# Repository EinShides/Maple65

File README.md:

A 65% standard single layout PCB that supports both cherry and alps switches. Uses USB mini with no ESD protection diode. PCB has been tested and is working.

Application: KiCad
Version: (5.1.5)-3, release build
Libraries:
    wxWidgets 3.0.4
    libcurl/7.66.0 OpenSSL/1.1.1d (Schannel) zlib/1.2.11 brotli/1.0.7 libidn2/2.2.0 libpsl/0.21.0 (+libidn2/2.1.1) nghttp2/1.39.2
Platform: Windows 8 (build 9200), 64-bit edition, 64 bit, Little endian, wxMSW
Build Info:
    wxWidgets: 3.0.4 (wchar_t,wx containers,compatible with 2.8)
    Boost: 1.71.0
    OpenCASCADE Community Edition: 6.9.1
    Curl: 7.66.0
    Compiler: GCC 9.2.0 with C++ ABI 1013

Build settings:
    USE_WX_GRAPHICS_CONTEXT=OFF
    USE_WX_OVERLAY=OFF
    KICAD_SCRIPTING=ON
    KICAD_SCRIPTING_MODULES=ON
    KICAD_SCRIPTING_PYTHON3=OFF
    KICAD_SCRIPTING_WXPYTHON=ON
    KICAD_SCRIPTING_WXPYTHON_PHOENIX=OFF
    KICAD_SCRIPTING_ACTION_MENU=ON
    BUILD_GITHUB_PLUGIN=ON
    KICAD_USE_OCE=ON
    KICAD_USE_OCC=OFF
    KICAD_SPICE=ON

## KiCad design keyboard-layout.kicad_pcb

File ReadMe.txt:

The Maple65 Keyboard is a 65% keyboard (303x94mm) that is based off of the Tada68 (same mounting holes and default layout)

IMPORTANT: Make sure to check and meet the design rules of the chosen pcb manufacturer before ordering or else errors may occur.
		e.g. OSH Park requires a Pad Mask Clearance of 0.0508mm

This CAD file was created in Kicad version (5.1.5)-3, release build.

Application: KiCad
Version: (5.1.5)-3, release build
Libraries:
    wxWidgets 3.0.4
    libcurl/7.66.0 OpenSSL/1.1.1d (Schannel) zlib/1.2.11 brotli/1.0.7 libidn2/2.2.0 libpsl/0.21.0 (+libidn2/2.1.1) nghttp2/1.39.2
Platform: Windows 8 (build 9200), 64-bit edition, 64 bit, Little endian, wxMSW
Build Info:
    wxWidgets: 3.0.4 (wchar_t,wx containers,compatible with 2.8)
    Boost: 1.71.0
    OpenCASCADE Community Edition: 6.9.1
    Curl: 7.66.0
    Compiler: GCC 9.2.0 with C++ ABI 1013

Build settings:
    USE_WX_GRAPHICS_CONTEXT=OFF
    USE_WX_OVERLAY=OFF
    KICAD_SCRIPTING=ON
    KICAD_SCRIPTING_MODULES=ON
    KICAD_SCRIPTING_PYTHON3=OFF
    KICAD_SCRIPTING_WXPYTHON=ON
    KICAD_SCRIPTING_WXPYTHON_PHOENIX=OFF
    KICAD_SCRIPTING_ACTION_MENU=ON
    BUILD_GITHUB_PLUGIN=ON
    KICAD_USE_OCE=ON
    KICAD_USE_OCC=OFF
    KICAD_SPICE=ON

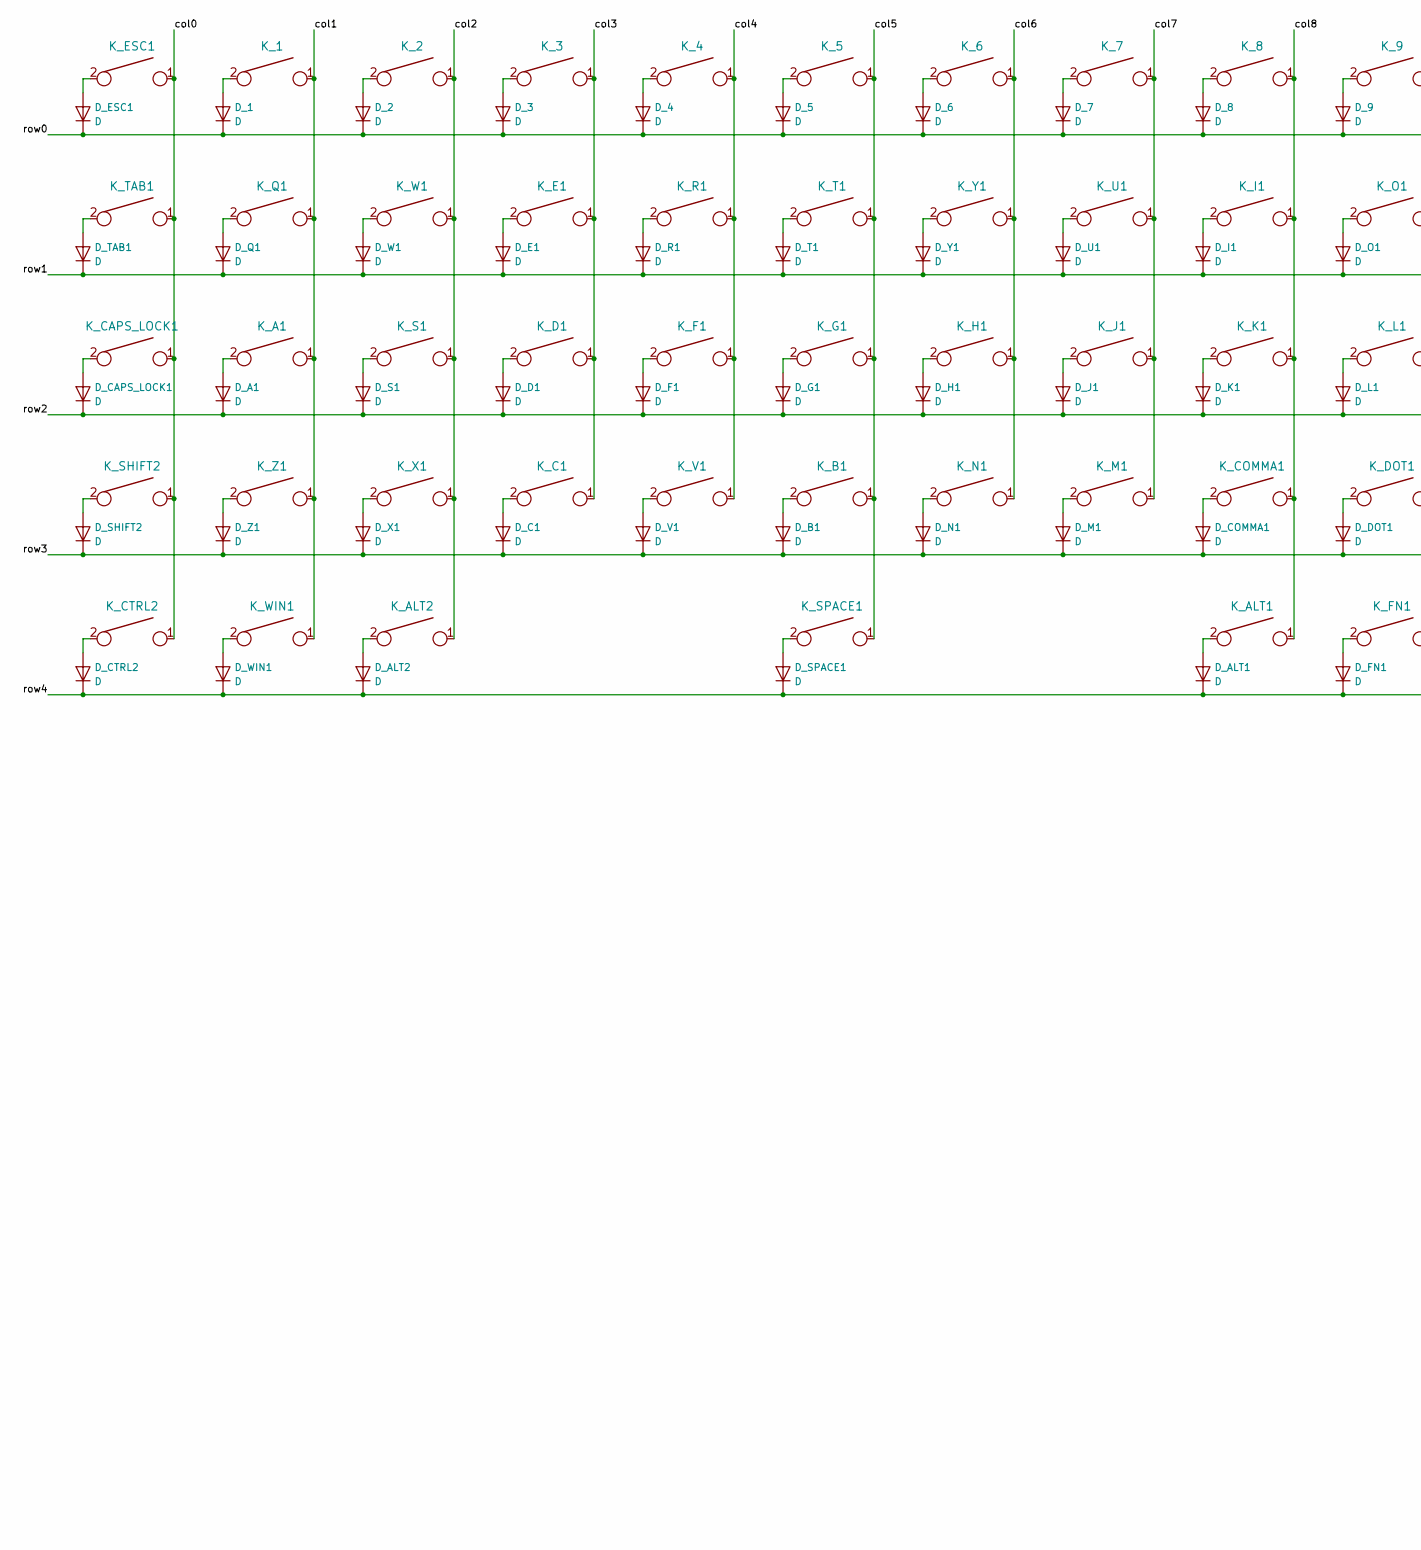
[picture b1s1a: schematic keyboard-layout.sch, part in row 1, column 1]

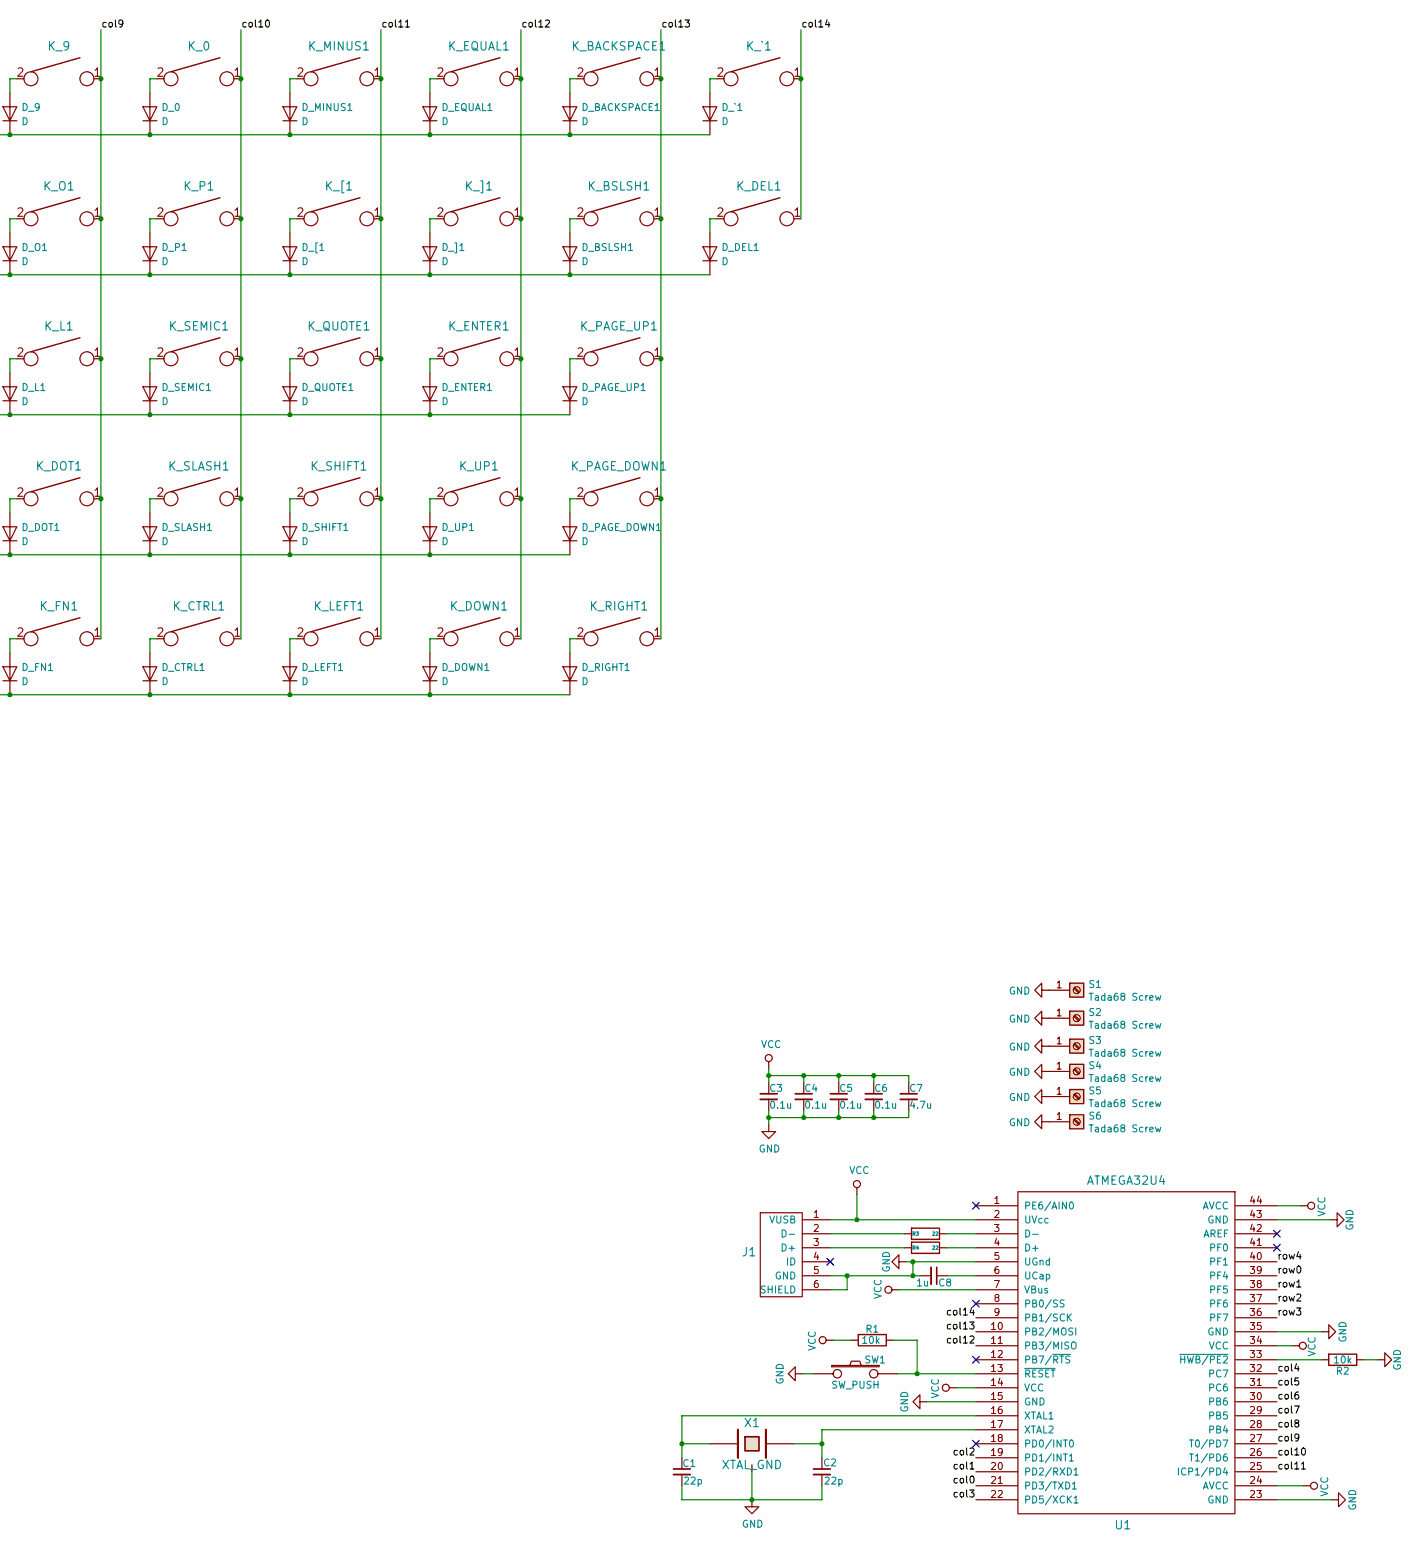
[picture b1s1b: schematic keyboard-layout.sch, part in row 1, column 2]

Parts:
C1, C2: 22p; C_0805_2012Metric_Pad1.15x1.40mm_HandSolder
C3, C4, C5, C6: 0.1u; C_0805_2012Metric_Pad1.15x1.40mm_HandSolder
C7: 4.7u; C_0805_2012Metric_Pad1.15x1.40mm_HandSolder
C8: 1u; C_0805_2012Metric_Pad1.15x1.40mm_HandSolder
D_0, D_1, D_2, D_3, D_4, D_5, D_6, D_7, D_8, D_9: D; D_SOD123_axial
D_A1: D; D_SOD123_axial
D_ALT1, D_ALT2: D; D_SOD123_axial
D_B1: D; D_SOD123_axial
D_BACKSPACE1: D; D_SOD123_axial
D_BSLSH1: D; D_SOD123_axial
D_C1: D; D_SOD123_axial
D_CAPS_LOCK1: D; D_SOD123_axial
D_COMMA1: D; D_SOD123_axial
D_CTRL1, D_CTRL2: D; D_SOD123_axial
D_D1: D; D_SOD123_axial
D_DEL1: D; D_SOD123_axial
D_DOT1: D; D_SOD123_axial
D_DOWN1: D; D_SOD123_axial
D_E1: D; D_SOD123_axial
D_ENTER1: D; D_SOD123_axial
D_EQUAL1: D; D_SOD123_axial
D_ESC1: D; D_SOD123_axial
D_F1: D; D_SOD123_axial
D_FN1: D; D_SOD123_axial
D_G1: D; D_SOD123_axial
D_H1: D; D_SOD123_axial
D_I1: D; D_SOD123_axial
D_J1: D; D_SOD123_axial
D_K1: D; D_SOD123_axial
D_L1: D; D_SOD123_axial
D_LEFT1: D; D_SOD123_axial
D_M1: D; D_SOD123_axial
D_MINUS1: D; D_SOD123_axial
D_N1: D; D_SOD123_axial
D_O1: D; D_SOD123_axial
D_P1: D; D_SOD123_axial
D_PAGE_DOWN1: D; D_SOD123_axial
D_PAGE_UP1: D; D_SOD123_axial
D_Q1: D; D_SOD123_axial
D_QUOTE1: D; D_SOD123_axial
D_R1: D; D_SOD123_axial
D_RIGHT1: D; D_SOD123_axial
D_S1: D; D_SOD123_axial
D_SEMIC1: D; D_SOD123_axial
D_SHIFT1, D_SHIFT2: D; D_SOD123_axial
D_SLASH1: D; D_SOD123_axial
D_SPACE1: D; D_SOD123_axial
D_T1: D; D_SOD123_axial
D_TAB1: D; D_SOD123_axial
D_U1: D; D_SOD123_axial
D_UP1: D; D_SOD123_axial
D_V1: D; D_SOD123_axial
D_W1: D; D_SOD123_axial
D_WIN1: D; D_SOD123_axial
D_X1: D; D_SOD123_axial
D_Y1: D; D_SOD123_axial
D_Z1: D; D_SOD123_axial
D_[1: D; D_SOD123_axial
D_]1: D; D_SOD123_axial
D_`1: D; D_SOD123_axial
J1: USB_mini_micro_B; USB_miniB_hirose_5S8
K_0, K_1, K_2, K_3, K_4, K_5, K_6, K_7, K_8, K_9: KEYSW; MX-1U-NoLED
K_A1: KEYSW; MX-1U-NoLED
K_ALT1: KEYSW; MX-1U-NoLED
K_ALT2: KEYSW; MX-1.25U-NoLED
K_B1: KEYSW; MX-1U-NoLED
K_BACKSPACE1: KEYSW; MX-2U-NoLED
K_BSLSH1: KEYSW; MX-1.5U-NoLED
K_C1: KEYSW; MX-1U-NoLED
K_CAPS_LOCK1: KEYSW; MX-1.75U-NoLED
K_COMMA1: KEYSW; MX-1U-NoLED
K_CTRL1: KEYSW; MX-1U-NoLED
K_CTRL2: KEYSW; MX-1.25U-NoLED
K_D1: KEYSW; MX-1U-NoLED
K_DEL1: KEYSW; MX-1U-NoLED
K_DOT1: KEYSW; MX-1U-NoLED
K_DOWN1: KEYSW; MX-1U-NoLED
K_E1: KEYSW; MX-1U-NoLED
K_ENTER1: KEYSW; MX-2.25U-NoLED
K_EQUAL1: KEYSW; MX-1U-NoLED
K_ESC1: KEYSW; MX-1U-NoLED
K_F1: KEYSW; MX-1U-NoLED
K_FN1: KEYSW; MX-1U-NoLED
K_G1: KEYSW; MX-1U-NoLED
K_H1: KEYSW; MX-1U-NoLED
K_I1: KEYSW; MX-1U-NoLED
K_J1: KEYSW; MX-1U-NoLED
K_K1: KEYSW; MX-1U-NoLED
K_L1: KEYSW; MX-1U-NoLED
K_LEFT1: KEYSW; MX-1U-NoLED
K_M1: KEYSW; MX-1U-NoLED
K_MINUS1: KEYSW; MX-1U-NoLED
K_N1: KEYSW; MX-1U-NoLED
K_O1: KEYSW; MX-1U-NoLED
K_P1: KEYSW; MX-1U-NoLED
K_PAGE_DOWN1: KEYSW; MX-1U-NoLED
K_PAGE_UP1: KEYSW; MX-1U-NoLED
K_Q1: KEYSW; MX-1U-NoLED
K_QUOTE1: KEYSW; MX-1U-NoLED
K_R1: KEYSW; MX-1U-NoLED
K_RIGHT1: KEYSW; MX-1U-NoLED
K_S1: KEYSW; MX-1U-NoLED
K_SEMIC1: KEYSW; MX-1U-NoLED
K_SHIFT1: KEYSW; MX-1.75U-NoLED
K_SHIFT2: KEYSW; MX-2.25U-NoLED
K_SLASH1: KEYSW; MX-1U-NoLED
K_SPACE1: KEYSW; MX-6.25U-ReversedStabilizers-NoLED
K_T1: KEYSW; MX-1U-NoLED
K_TAB1: KEYSW; MX-1.5U-NoLED
K_U1: KEYSW; MX-1U-NoLED
K_UP1: KEYSW; MX-1U-NoLED
K_V1: KEYSW; MX-1U-NoLED
K_W1: KEYSW; MX-1U-NoLED
K_WIN1: KEYSW; MX-1.25U-NoLED
K_X1: KEYSW; MX-1U-NoLED
K_Y1: KEYSW; MX-1U-NoLED
K_Z1: KEYSW; MX-1U-NoLED
K_[1: KEYSW; MX-1U-NoLED
K_]1: KEYSW; MX-1U-NoLED
K_`1: KEYSW; MX-1U-NoLED
R1, R2: 10k; R_0805_2012Metric_Pad1.15x1.40mm_HandSolder
R3, R4: 22; R_0805_2012Metric_Pad1.15x1.40mm_HandSolder
S1, S2, S3, S4, S5, S6: Tada68 Screw; 5.5_5x2.5mm
SW1: SW_PUSH; SW_SPST_TL3342
U1: ATMEGA32U4; TQFP-44_10x10mm_Pitch0.8mm
X1: XTAL_GND; crystal_FA238-TSX3225

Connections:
/col0: K_CAPS_LOCK1.1, K_CTRL2.1, K_ESC1.1, K_SHIFT2.1, K_TAB1.1, U1.21 (PD3/TXD1)
/col1: K_1.1, K_A1.1, K_Q1.1, K_WIN1.1, K_Z1.1, U1.20 (PD2/RXD1)
/col2: K_2.1, K_ALT2.1, K_S1.1, K_W1.1, K_X1.1, U1.19 (PD1/INT1)
/col3: K_3.1, K_C1.1, K_D1.1, K_E1.1, U1.22 (PD5/XCK1)
/col4: K_4.1, K_F1.1, K_R1.1, K_V1.1, U1.32 (PC7)
/col5: K_5.1, K_B1.1, K_G1.1, K_SPACE1.1, K_T1.1, U1.31 (PC6)
/col6: K_6.1, K_H1.1, K_N1.1, K_Y1.1, U1.30 (PB6)
/col7: K_7.1, K_J1.1, K_M1.1, K_U1.1, U1.29 (PB5)
/col8: K_8.1, K_ALT1.1, K_COMMA1.1, K_I1.1, K_K1.1, U1.28 (PB4)
/col9: K_9.1, K_DOT1.1, K_FN1.1, K_L1.1, K_O1.1, U1.27 (T0/PD7)
/col10: K_0.1, K_CTRL1.1, K_P1.1, K_SEMIC1.1, K_SLASH1.1, U1.26 (T1/PD6)
/col11: K_LEFT1.1, K_MINUS1.1, K_QUOTE1.1, K_SHIFT1.1, K_[1.1, U1.25 (ICP1/PD4)
/col12: K_DOWN1.1, K_ENTER1.1, K_EQUAL1.1, K_UP1.1, K_]1.1, U1.11 (PB3/MISO)
/col13: K_BACKSPACE1.1, K_BSLSH1.1, K_PAGE_DOWN1.1, K_PAGE_UP1.1, K_RIGHT1.1, U1.10 (PB2/MOSI)
/col14: K_DEL1.1, K_`1.1, U1.9 (PB1/SCK)
/row0: D_0.1 (K), D_1.1 (K), D_2.1 (K), D_3.1 (K), D_4.1 (K), D_5.1 (K), D_6.1 (K), D_7.1 (K), D_8.1 (K), D_9.1 (K), D_BACKSPACE1.1 (K), D_EQUAL1.1 (K), D_ESC1.1 (K), D_MINUS1.1 (K), D_`1.1 (K), U1.39 (PF4)
/row1: D_BSLSH1.1 (K), D_DEL1.1 (K), D_E1.1 (K), D_I1.1 (K), D_O1.1 (K), D_P1.1 (K), D_Q1.1 (K), D_R1.1 (K), D_T1.1 (K), D_TAB1.1 (K), D_U1.1 (K), D_W1.1 (K), D_Y1.1 (K), D_[1.1 (K), D_]1.1 (K), U1.38 (PF5)
/row2: D_A1.1 (K), D_CAPS_LOCK1.1 (K), D_D1.1 (K), D_ENTER1.1 (K), D_F1.1 (K), D_G1.1 (K), D_H1.1 (K), D_J1.1 (K), D_K1.1 (K), D_L1.1 (K), D_PAGE_UP1.1 (K), D_QUOTE1.1 (K), D_S1.1 (K), D_SEMIC1.1 (K), U1.37 (PF6)
/row3: D_B1.1 (K), D_C1.1 (K), D_COMMA1.1 (K), D_DOT1.1 (K), D_M1.1 (K), D_N1.1 (K), D_PAGE_DOWN1.1 (K), D_SHIFT1.1 (K), D_SHIFT2.1 (K), D_SLASH1.1 (K), D_UP1.1 (K), D_V1.1 (K), D_X1.1 (K), D_Z1.1 (K), U1.36 (PF7)
/row4: D_ALT1.1 (K), D_ALT2.1 (K), D_CTRL1.1 (K), D_CTRL2.1 (K), D_DOWN1.1 (K), D_FN1.1 (K), D_LEFT1.1 (K), D_RIGHT1.1 (K), D_SPACE1.1 (K), D_WIN1.1 (K), U1.40 (PF1)
GND: C1.2, C2.2, C3.2, C4.2, C5.2, C6.2, C7.2, C8.2, J1.5 (GND), J1.6 (SHIELD), R2.1, S1.1, S2.1, S3.1, S4.1, S5.1, S6.1, SW1.1, U1.5 (UGnd), U1.15 (GND), U1.23 (GND), U1.35 (GND), U1.43 (GND), X1.3
unnamed: C1.1, U1.16 (XTAL1), X1.1
unnamed: C2.1, U1.17 (XTAL2), X1.2
unnamed: C8.1, U1.6 (UCap)
unnamed: D_0.2 (A), K_0.2
unnamed: D_1.2 (A), K_1.2
unnamed: D_2.2 (A), K_2.2
unnamed: D_3.2 (A), K_3.2
unnamed: D_4.2 (A), K_4.2
unnamed: D_5.2 (A), K_5.2
unnamed: D_6.2 (A), K_6.2
unnamed: D_7.2 (A), K_7.2
unnamed: D_8.2 (A), K_8.2
unnamed: D_9.2 (A), K_9.2
unnamed: D_A1.2 (A), K_A1.2
unnamed: D_ALT1.2 (A), K_ALT1.2
unnamed: D_ALT2.2 (A), K_ALT2.2
unnamed: D_B1.2 (A), K_B1.2
unnamed: D_BACKSPACE1.2 (A), K_BACKSPACE1.2
unnamed: D_BSLSH1.2 (A), K_BSLSH1.2
unnamed: D_C1.2 (A), K_C1.2
unnamed: D_CAPS_LOCK1.2 (A), K_CAPS_LOCK1.2
unnamed: D_COMMA1.2 (A), K_COMMA1.2
unnamed: D_CTRL1.2 (A), K_CTRL1.2
unnamed: D_CTRL2.2 (A), K_CTRL2.2
unnamed: D_D1.2 (A), K_D1.2
unnamed: D_DEL1.2 (A), K_DEL1.2
unnamed: D_DOT1.2 (A), K_DOT1.2
unnamed: D_DOWN1.2 (A), K_DOWN1.2
unnamed: D_E1.2 (A), K_E1.2
unnamed: D_ENTER1.2 (A), K_ENTER1.2
unnamed: D_EQUAL1.2 (A), K_EQUAL1.2
unnamed: D_ESC1.2 (A), K_ESC1.2
unnamed: D_F1.2 (A), K_F1.2
unnamed: D_FN1.2 (A), K_FN1.2
unnamed: D_G1.2 (A), K_G1.2
unnamed: D_H1.2 (A), K_H1.2
unnamed: D_I1.2 (A), K_I1.2
unnamed: D_J1.2 (A), K_J1.2
unnamed: D_K1.2 (A), K_K1.2
unnamed: D_L1.2 (A), K_L1.2
unnamed: D_LEFT1.2 (A), K_LEFT1.2
unnamed: D_M1.2 (A), K_M1.2
unnamed: D_MINUS1.2 (A), K_MINUS1.2
unnamed: D_N1.2 (A), K_N1.2
unnamed: D_O1.2 (A), K_O1.2
unnamed: D_P1.2 (A), K_P1.2
unnamed: D_PAGE_DOWN1.2 (A), K_PAGE_DOWN1.2
unnamed: D_PAGE_UP1.2 (A), K_PAGE_UP1.2
unnamed: D_Q1.2 (A), K_Q1.2
unnamed: D_QUOTE1.2 (A), K_QUOTE1.2
unnamed: D_R1.2 (A), K_R1.2
unnamed: D_RIGHT1.2 (A), K_RIGHT1.2
unnamed: D_S1.2 (A), K_S1.2
unnamed: D_SEMIC1.2 (A), K_SEMIC1.2
unnamed: D_SHIFT1.2 (A), K_SHIFT1.2
unnamed: D_SHIFT2.2 (A), K_SHIFT2.2
unnamed: D_SLASH1.2 (A), K_SLASH1.2
unnamed: D_SPACE1.2 (A), K_SPACE1.2
unnamed: D_T1.2 (A), K_T1.2
unnamed: D_TAB1.2 (A), K_TAB1.2
unnamed: D_U1.2 (A), K_U1.2
unnamed: D_UP1.2 (A), K_UP1.2
unnamed: D_V1.2 (A), K_V1.2
unnamed: D_W1.2 (A), K_W1.2
unnamed: D_WIN1.2 (A), K_WIN1.2
unnamed: D_X1.2 (A), K_X1.2
unnamed: D_Y1.2 (A), K_Y1.2
unnamed: D_Z1.2 (A), K_Z1.2
unnamed: D_[1.2 (A), K_[1.2
unnamed: D_]1.2 (A), K_]1.2
unnamed: D_`1.2 (A), K_`1.2
unnamed: J1.2 (D-), R3.2
unnamed: J1.3 (D+), R4.2
unnamed: R1.1, SW1.2, U1.13 (~RESET)
unnamed: R2.2, U1.33 (~HWB/PE2)
unnamed: R3.1, U1.3 (D-)
unnamed: R4.1, U1.4 (D+)
VCC: C3.1, C4.1, C5.1, C6.1, C7.1, J1.1 (VUSB), R1.2, U1.2 (UVcc), U1.7 (VBus), U1.14 (VCC), U1.24 (AVCC), U1.34 (VCC), U1.44 (AVCC)

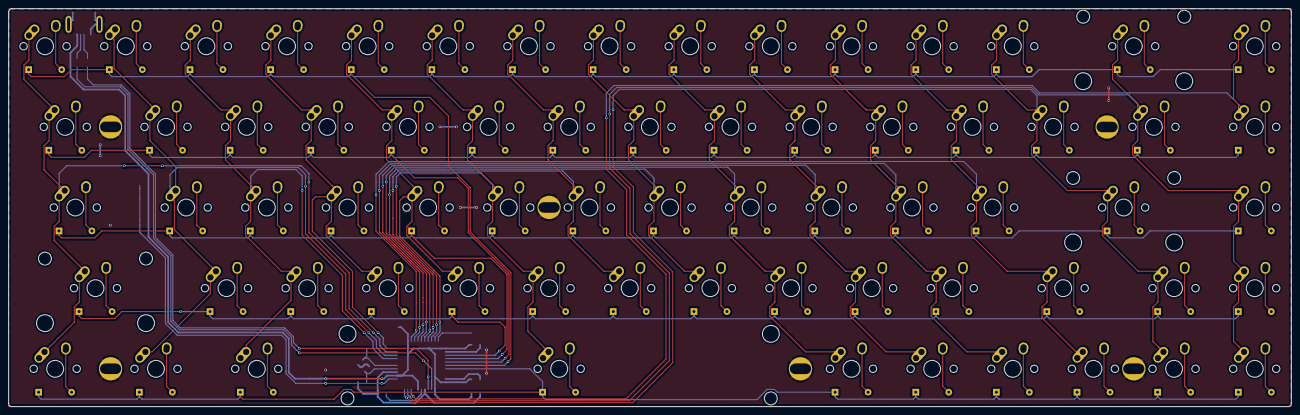
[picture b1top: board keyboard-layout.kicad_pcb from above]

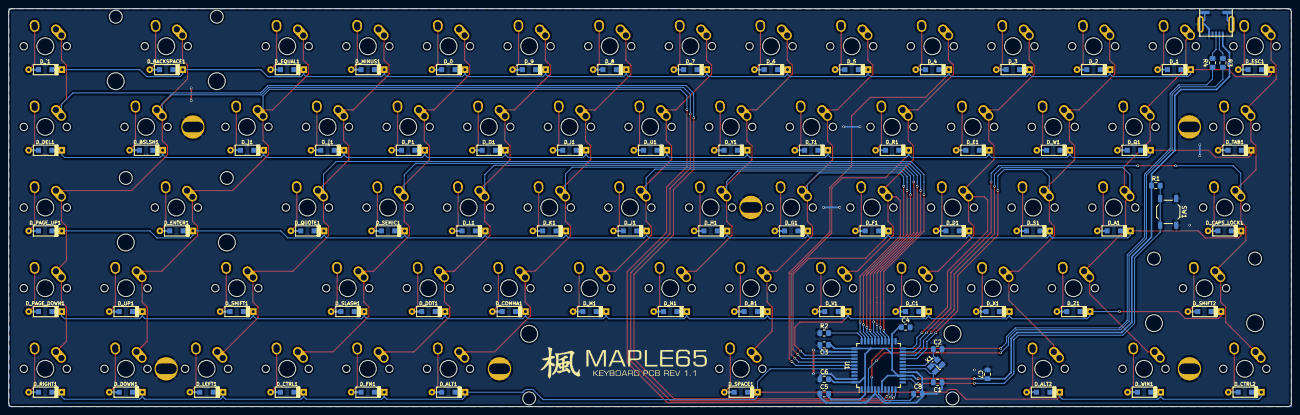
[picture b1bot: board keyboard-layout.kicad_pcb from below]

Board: 2 copper layers, 303.0 x 94.0 mm, 158 parts (84 on the bottom side), 99 nets.
